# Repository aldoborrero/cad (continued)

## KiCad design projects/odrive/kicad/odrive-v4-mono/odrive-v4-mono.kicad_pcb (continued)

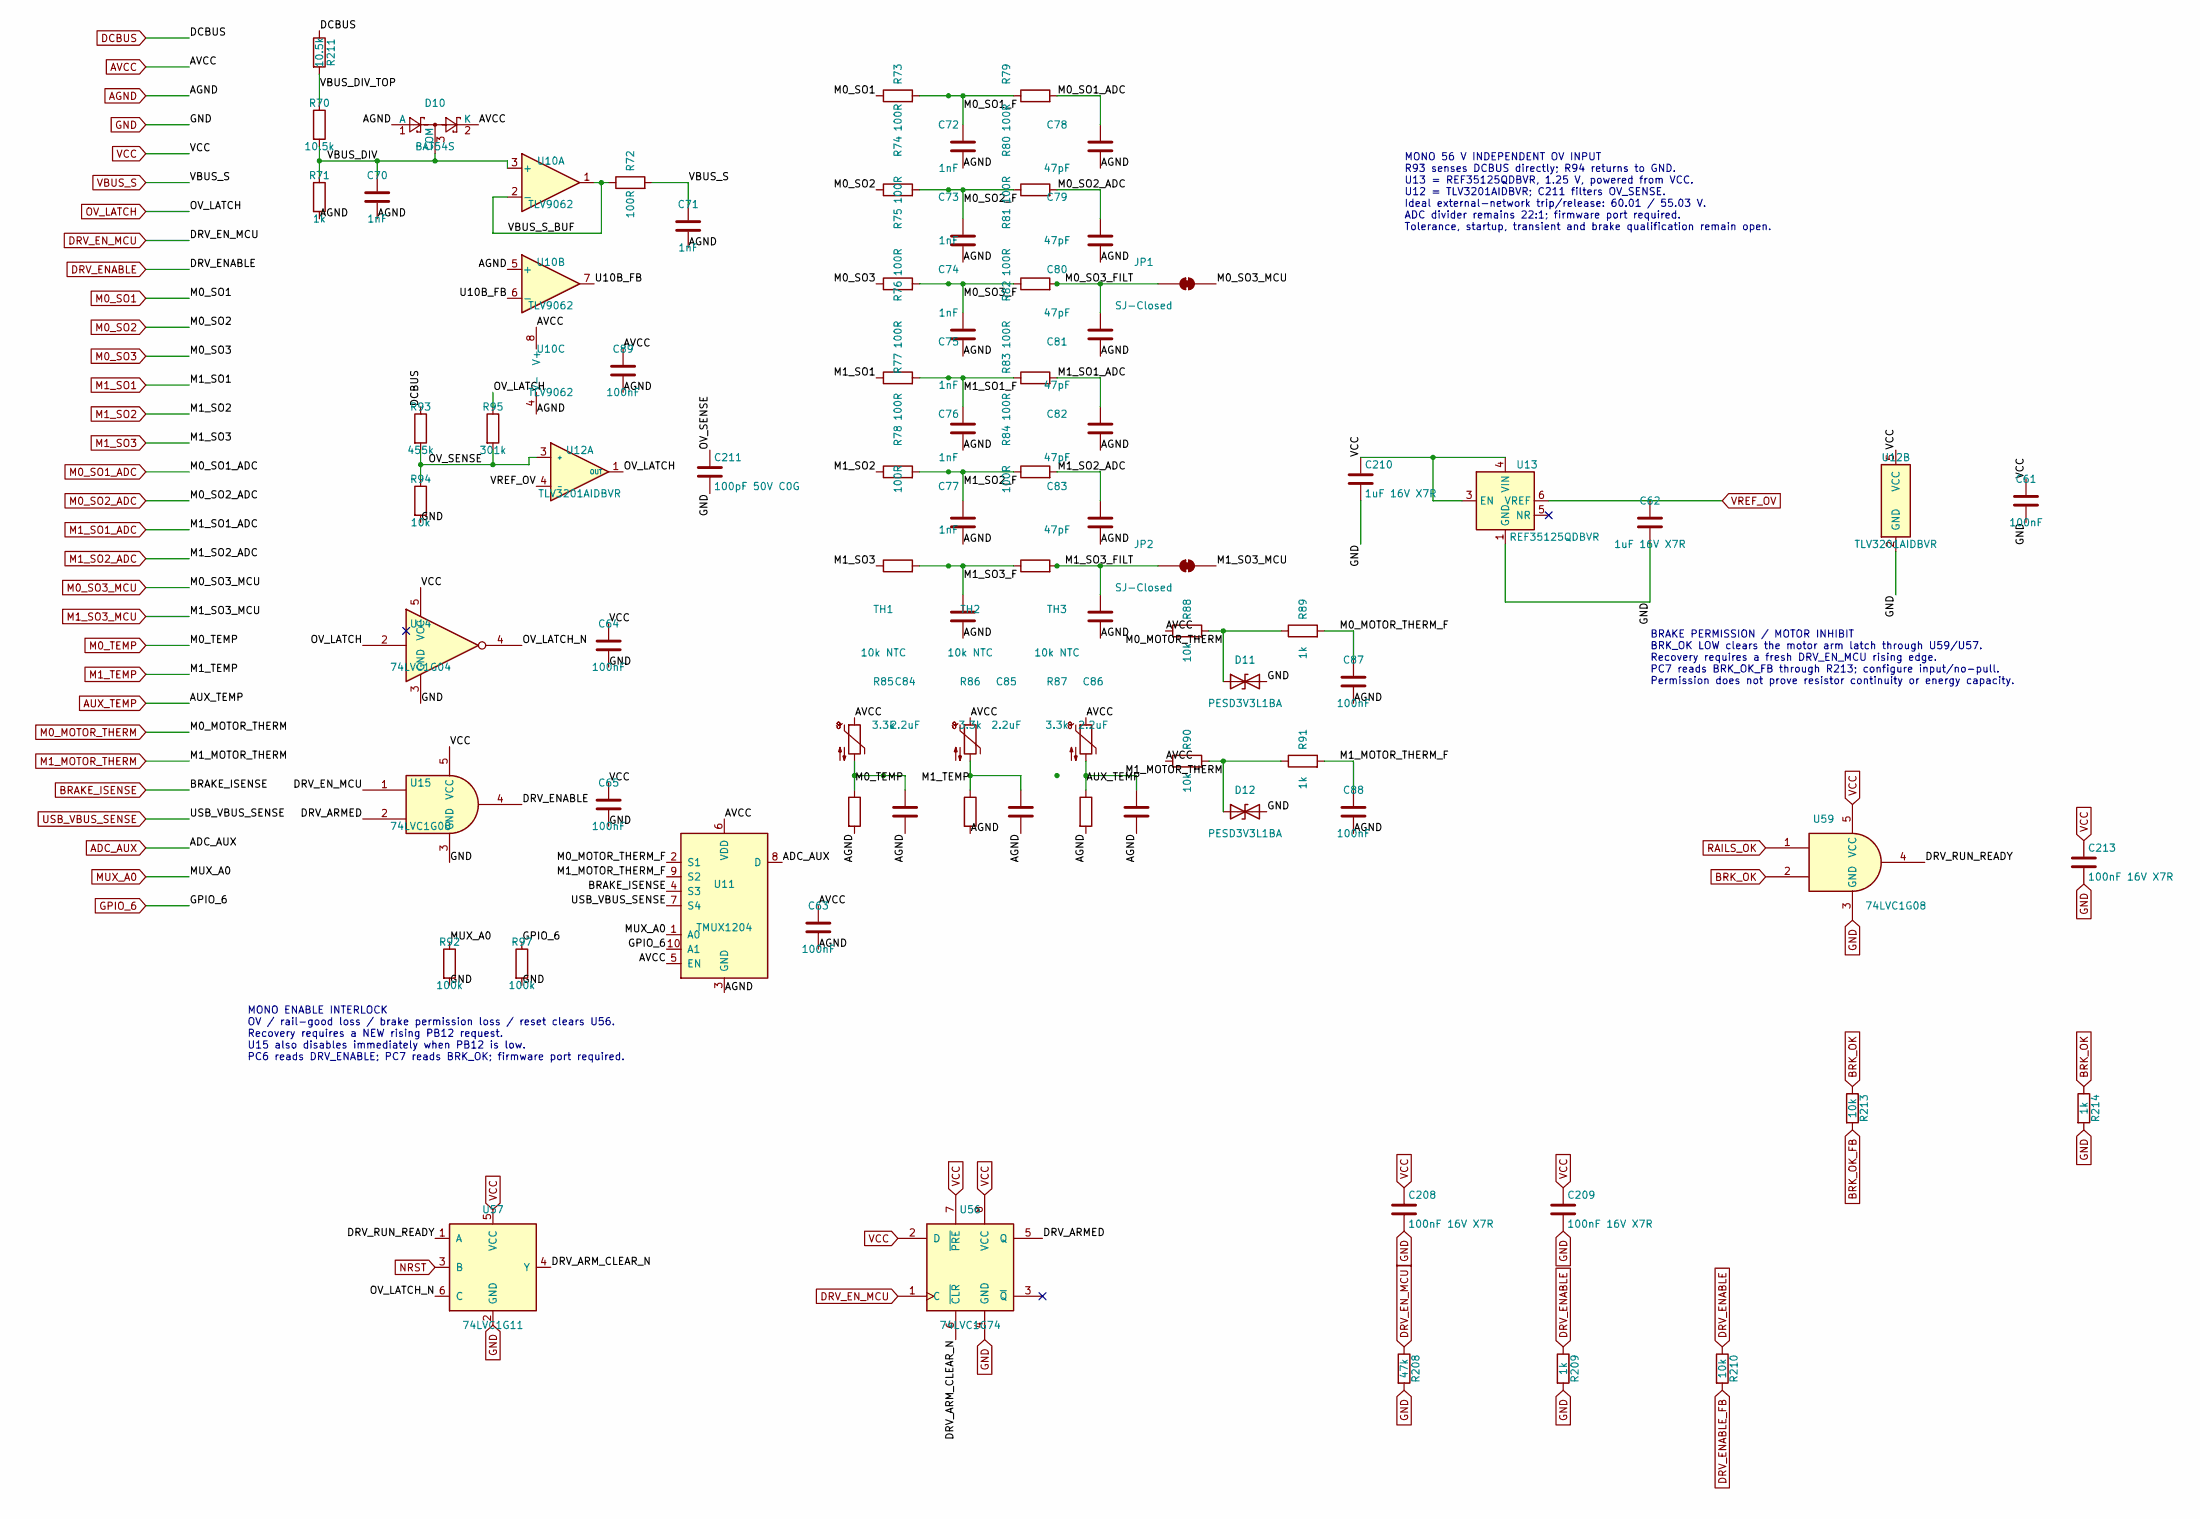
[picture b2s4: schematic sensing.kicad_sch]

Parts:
C61, C63, C64, C65, C87, C88, C89: 100nF; C_0603_1608Metric
C62, C210: 1uF 16V X7R; C_0603_1608Metric; Tolerance 10%
C70, C71, C72, C73, C74, C75, C76, C77: 1nF; C_0603_1608Metric
C78, C79, C80, C81, C82, C83: 47pF; C_0603_1608Metric
C84, C85, C86: 2.2uF; C_0603_1608Metric
C208, C209: 100nF 16V X7R; C_0603_1608Metric
C211: 100pF 50V C0G; C_0603_1608Metric; Tolerance 5%
C213: 100nF 16V X7R; C_0603_1608Metric; Tolerance 10%
D10: BAT54S; SOT-23
D11, D12: PESD3V3L1BA; D_SOD-323
JP1, JP2: SJ-Closed; SolderJumper-2_P1.3mm_Bridged_Pad1.0x1.5mm
R70, R211: 10.5k; R_1206_3216Metric; Tolerance 0.1%; Voltage 200 V minimum working
R71: 1k; R_0603_1608Metric; Tolerance 0.1%
R72, R73, R74, R75, R76, R77, R78, R79, R80, R81, R82, R83, R84: 100R; R_0603_1608Metric
R85, R86, R87: 3.3k; R_0603_1608Metric
R88, R90: 10k; R_0603_1608Metric
R89, R91: 1k; R_0603_1608Metric
R92, R97: 100k; R_0603_1608Metric
R93: 455k; R_1206_3216Metric; Tolerance 0.1%; Working voltage 200 V minimum
R94: 10k; R_0603_1608Metric; Tolerance 0.1%
R95: 301k; R_0603_1608Metric; Tolerance 0.1%
R208: 47k; R_0603_1608Metric; Tolerance 1%
R209, R214: 1k; R_0603_1608Metric; Tolerance 1%
R210, R213: 10k; R_0603_1608Metric; Tolerance 1%
TH1, TH2, TH3: 10k NTC; R_0603_1608Metric
U10: TLV9062; SOIC-8_3.9x4.9mm_P1.27mm
U11: TMUX1204; MSOP-10_3x3mm_P0.5mm; MPN TMUX1204DGSR
U12: TLV3201AIDBVR; SOT-23-5; MPN TLV3201AIDBVR
U13: REF35125QDBVR; SOT-23-6; MPN REF35125QDBVR
U14: 74LVC1G04; SOT-23-5; MPN SN74LVC1G04DBVR
U15, U59: 74LVC1G08; SOT-23-5; MPN SN74LVC1G08DBVR
U56: 74LVC1G74; VSSOP-8_2.3x2mm_P0.5mm; MPN SN74LVC1G74DCUR
U57: 74LVC1G11; SOT-23-6; MPN SN74LVC1G11DBVR

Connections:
/Sensing/DRV_ARMED: U15.2, U56.5 (Q)
/Sensing/DRV_ARM_CLEAR_N: U56.6 (~CLR), U57.4 (Y)
/Sensing/DRV_RUN_READY: U57.1 (A), U59.4
/Sensing/M0_MOTOR_THERM_F: C87.1, R89.2, U11.2 (S1)
/Sensing/M0_SO1_F: C72.1, R73.2, R79.1
/Sensing/M0_SO2_F: C73.1, R74.2, R80.1
/Sensing/M0_SO3_F: C76.1, R77.2, R83.1
/Sensing/M0_SO3_FILT: C82.1, JP1.1 (A), R83.2
/Sensing/M1_MOTOR_THERM_F: C88.1, R91.2, U11.9 (S2)
/Sensing/M1_SO1_F: C75.1, R76.2, R82.1
/Sensing/M1_SO2_F: C74.1, R75.2, R81.1
/Sensing/M1_SO3_F: C77.1, R78.2, R84.1
/Sensing/M1_SO3_FILT: C83.1, JP2.1 (A), R84.2
/Sensing/OV_LATCH_N: U14.4, U57.6 (C)
/Sensing/OV_SENSE: C211.1, R93.2, R94.1, R95.2, U12.3 (+)
/Sensing/U10B_FB: U10.6 (-), U10.7
/Sensing/VBUS_DIV: C70.1, D10.3 (COM), R70.2, R71.1, U10.3 (+)
/Sensing/VBUS_DIV_TOP: R70.1, R211.2
/Sensing/VBUS_S_BUF: R72.1, U10.1, U10.2 (-)
ADC_AUX: U11.8 (D); also elsewhere on the board
AGND: C63.2, C70.2, C71.2, C72.2, C73.2, C74.2, C75.2, C76.2, C77.2, C78.2, C79.2, C80.2, C81.2, C82.2, C83.2, C84.2, C85.2, C86.2, C87.2, C88.2, C89.2, D10.1 (A), R71.2, R85.2, R86.2, R87.2, U10.4 (V-), U10.5 (+), U11.3 (GND); also elsewhere on the board
AUX_TEMP: C86.1, R87.1, TH3.2; also elsewhere on the board
AVCC: C63.1, C89.1, D10.2 (K), R88.1, R90.1, TH1.1, TH2.1, TH3.1, U10.8 (V+), U11.5 (EN), U11.6 (VDD); also elsewhere on the board
BRAKE_ISENSE: U11.4 (S3); also elsewhere on the board
BRK_OK: R213.1, R214.1, U59.2; also elsewhere on the board
BRK_OK_FB: R213.2; also elsewhere on the board
DCBUS: R93.1, R211.1; also elsewhere on the board
DRV_ENABLE: R209.1, R210.1, U15.4; also elsewhere on the board
DRV_ENABLE_FB: R210.2; also elsewhere on the board
DRV_EN_MCU: R208.1, U15.1, U56.1 (C); also elsewhere on the board
GND: C61.2, C62.2, C64.2, C65.2, C208.2, C209.2, C210.2, C211.2, C213.2, D11.2 (A2), D12.2 (A2), R92.2, R94.2, R97.2, R208.2, R209.2, R214.2, U12.2 (GND), U13.1 (GND), U13.2 (GND), U14.3 (GND), U15.3 (GND), U56.4 (GND), U57.2 (GND), U59.3 (GND); also elsewhere on the board
GPIO_6: R97.1, U11.10 (A1); also elsewhere on the board
M0_MOTOR_THERM: D11.1 (A1), R88.2, R89.1; also elsewhere on the board
M0_SO1: R73.1; also elsewhere on the board
M0_SO1_ADC: C78.1, R79.2; also elsewhere on the board
M0_SO2: R74.1; also elsewhere on the board
M0_SO2_ADC: C79.1, R80.2; also elsewhere on the board
M0_SO3: R77.1; also elsewhere on the board
M0_SO3_MCU: JP1.2 (B); also elsewhere on the board
M0_TEMP: C84.1, R85.1, TH1.2; also elsewhere on the board
M1_MOTOR_THERM: D12.1 (A1), R90.2, R91.1; also elsewhere on the board
M1_SO1: R76.1
M1_SO1_ADC: C81.1, R82.2; also elsewhere on the board
M1_SO2: R75.1
M1_SO2_ADC: C80.1, R81.2; also elsewhere on the board
M1_SO3: R78.1
M1_SO3_MCU: JP2.2 (B); also elsewhere on the board
M1_TEMP: C85.1, R86.1, TH2.2; also elsewhere on the board
MUX_A0: R92.1, U11.1 (A0); also elsewhere on the board
NRST: U57.3 (B); also elsewhere on the board
OV_LATCH: R95.1, U12.1 (OUT), U14.2; also elsewhere on the board
RAILS_OK: U59.1; also elsewhere on the board
USB_VBUS_SENSE: U11.7 (S4); also elsewhere on the board
VBUS_S: C71.1, R72.2; also elsewhere on the board
VCC: C61.1, C64.1, C65.1, C208.1, C209.1, C210.1, C213.1, U12.5 (VCC), U13.3 (EN), U13.4 (VIN), U14.5 (VCC), U15.5 (VCC), U56.2 (D), U56.7 (~PRE), U56.8 (VCC), U57.5 (VCC), U59.5 (VCC); also elsewhere on the board
VREF_OV: C62.1, U12.4 (-), U13.6 (VREF); also elsewhere on the board

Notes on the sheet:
MONO 56 V INDEPENDENT OV INPUT R93 senses DCBUS directly; R94 returns to GND. U13 = REF35125QDBVR, 1.25 V, powered from VCC. U12 = TLV3201AIDBVR; C211 filters OV_SENSE. Ideal external-network trip/release: 60.01 / 55.03 V. ADC divider remains 22:1; firmware port required. Tolerance, startup, transi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
BRAKE PERMISSION / MOTOR INHIBIT BRK_OK LOW clears the motor arm latch through U59/U57. Recovery requires a fresh DRV_EN_MCU rising edge. PC7 reads BRK_OK_FB through R213; configure input/no-pull. Permission does not prove resistor continuity or energy capacity.
MONO ENABLE INTERLOCK OV / rail-good loss / brake permission loss / reset clears U56. Recovery requires a NEW rising PB12 request. U15 also disables immediately when PB12 is low. PC6 reads DRV_ENABLE; PC7 reads BRK_OK; firmware port required.

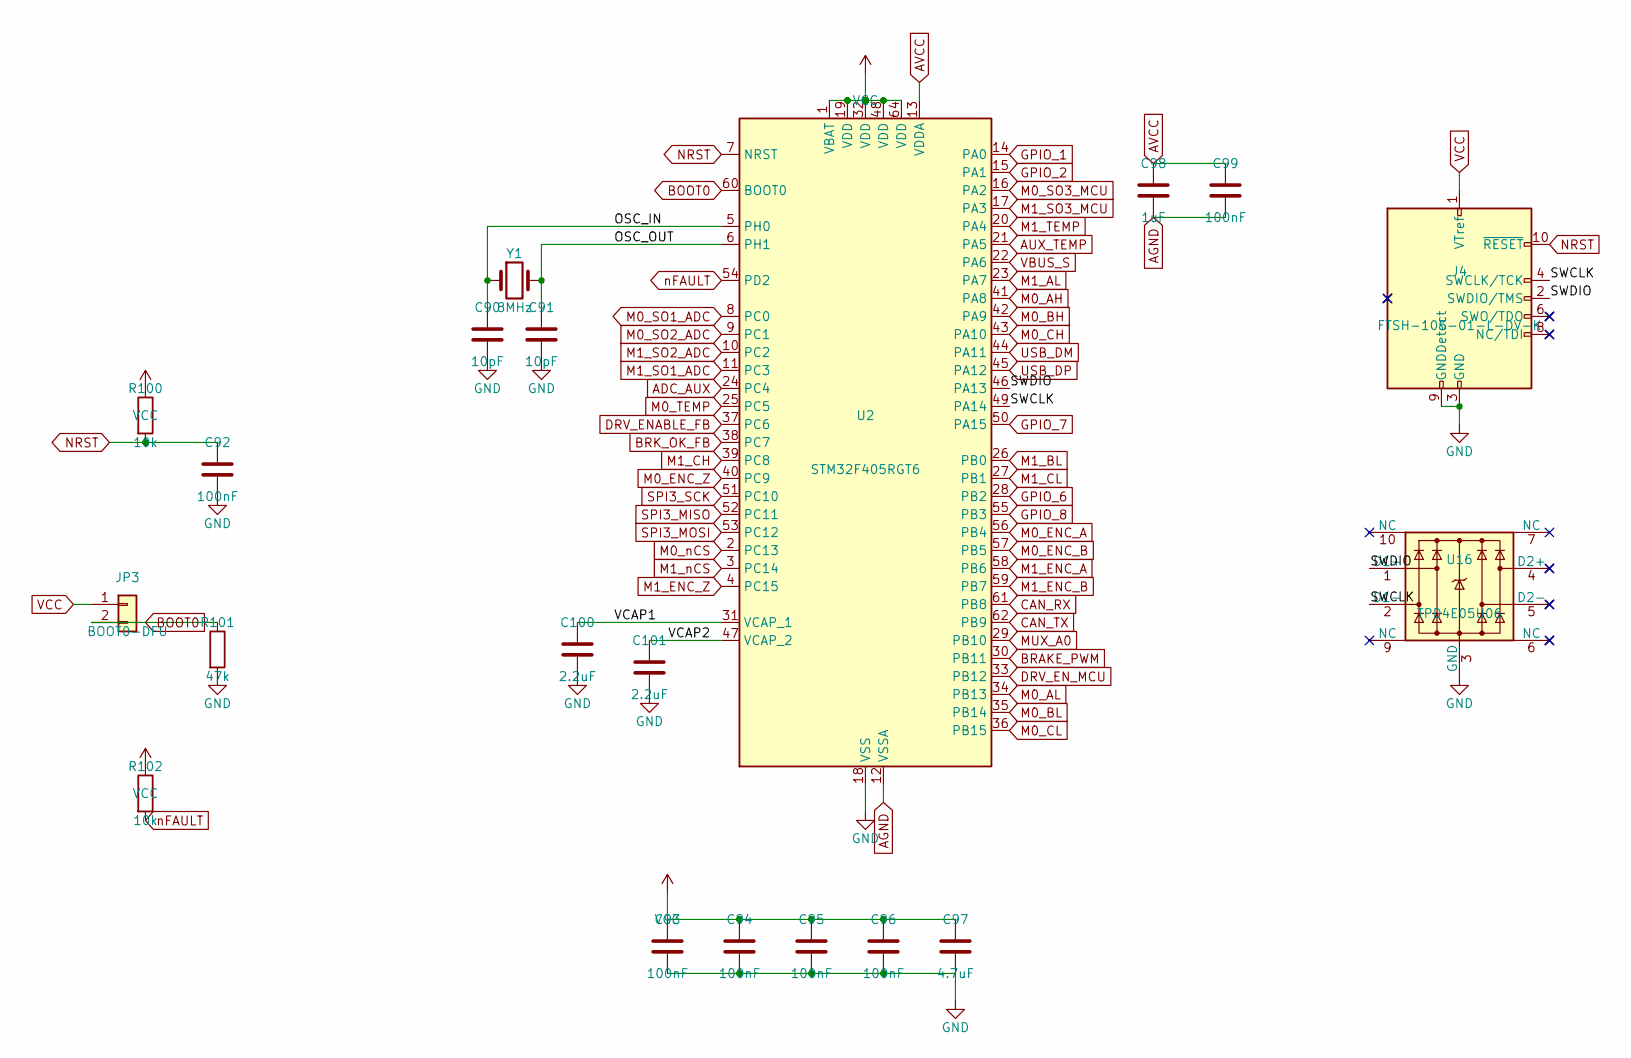
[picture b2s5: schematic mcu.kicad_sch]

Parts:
C90, C91: 10pF; C_0603_1608Metric
C92, C93, C94, C95, C96, C99: 100nF; C_0603_1608Metric
C97: 4.7uF; C_0805_2012Metric
C98: 1uF; C_0603_1608Metric
C100, C101: 2.2uF; C_0603_1608Metric
J4: FTSH-105-01-L-DV-K; PinHeader_2x05_P1.27mm_Vertical_SMD
JP3: BOOT0-DFU; PinHeader_1x02_P2.54mm_Vertical
R100, R102: 10k; R_0603_1608Metric
R101: 47k; R_0603_1608Metric
U2: STM32F405RGT6; LQFP-64_10x10mm_P0.5mm
U16: TPD4E05U06; USON-10_2.5x1.0mm_P0.5mm
Y1: 8MHz; Crystal_SMD_5032-2Pin_5.0x3.2mm

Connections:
/MCU/OSC_IN: C90.1, U2.5 (PH0), Y1.1
/MCU/OSC_OUT: C91.1, U2.6 (PH1), Y1.2
/MCU/SWCLK: J4.4 (SWCLK/TCK), U2.49 (PA14), U16.2 (D1-)
/MCU/SWDIO: J4.2 (SWDIO/TMS), U2.46 (PA13), U16.1 (D1+)
/MCU/VCAP1: C100.1, U2.31 (VCAP_1)
/MCU/VCAP2: C101.1, U2.47 (VCAP_2)
ADC_AUX: U2.24 (PC4); also elsewhere on the board
AGND: C98.2, C99.2, U2.12 (VSSA); also elsewhere on the board
AUX_TEMP: U2.21 (PA5); also elsewhere on the board
AVCC: C98.1, C99.1, U2.13 (VDDA); also elsewhere on the board
BOOT0: JP3.2, R101.1, U2.60 (BOOT0)
BRAKE_PWM: U2.30 (PB11); also elsewhere on the board
BRK_OK_FB: U2.38 (PC7); also elsewhere on the board
CAN_RX: U2.61 (PB8); also elsewhere on the board
CAN_TX: U2.62 (PB9); also elsewhere on the board
DRV_ENABLE_FB: U2.37 (PC6); also elsewhere on the board
DRV_EN_MCU: U2.33 (PB12); also elsewhere on the board
GND: C90.2, C91.2, C92.2, C93.2, C94.2, C95.2, C96.2, C97.2, C100.2, C101.2, J4.3 (GND), J4.5 (GND), J4.9 (GNDDetect), R101.2, U2.18 (VSS), U2.63 (VSS), U16.3 (GND), U16.8 (GND); also elsewhere on the board
GPIO_1: U2.14 (PA0); also elsewhere on the board
GPIO_2: U2.15 (PA1); also elsewhere on the board
GPIO_6: U2.28 (PB2); also elsewhere on the board
GPIO_7: U2.50 (PA15); also elsewhere on the board
GPIO_8: U2.55 (PB3); also elsewhere on the board
M0_AH: U2.41 (PA8); also elsewhere on the board
M0_AL: U2.34 (PB13); also elsewhere on the board
M0_BH: U2.42 (PA9); also elsewhere on the board
M0_BL: U2.35 (PB14); also elsewhere on the board
M0_CH: U2.43 (PA10); also elsewhere on the board
M0_CL: U2.36 (PB15); also elsewhere on the board
M0_ENC_A: U2.56 (PB4); also elsewhere on the board
M0_ENC_B: U2.57 (PB5); also elsewhere on the board
M0_ENC_Z: U2.40 (PC9); also elsewhere on the board
M0_SO1_ADC: U2.8 (PC0); also elsewhere on the board
M0_SO2_ADC: U2.9 (PC1); also elsewhere on the board
M0_SO3_MCU: U2.16 (PA2); also elsewhere on the board
M0_TEMP: U2.25 (PC5); also elsewhere on the board
M0_nCS: U2.2 (PC13); also elsewhere on the board
M1_AL: U2.23 (PA7)
M1_BL: U2.26 (PB0)
M1_CH: U2.39 (PC8)
M1_CL: U2.27 (PB1)
M1_ENC_A: U2.58 (PB6); also elsewhere on the board
M1_ENC_B: U2.59 (PB7); also elsewhere on the board
M1_ENC_Z: U2.4 (PC15); also elsewhere on the board
M1_SO1_ADC: U2.11 (PC3); also elsewhere on the board
M1_SO2_ADC: U2.10 (PC2); also elsewhere on the board
M1_SO3_MCU: U2.17 (PA3); also elsewhere on the board
M1_TEMP: U2.20 (PA4); also elsewhere on the board
M1_nCS: U2.3 (PC14)
MUX_A0: U2.29 (PB10); also elsewhere on the board
NRST: C92.1, J4.10 (~RESET), R100.2, U2.7 (NRST); also elsewhere on the board
SPI3_MISO: U2.52 (PC11); also elsewhere on the board
SPI3_MOSI: U2.53 (PC12); also elsewhere on the board
SPI3_SCK: U2.51 (PC10); also elsewhere on the board
USB_DM: U2.44 (PA11); also elsewhere on the board
USB_DP: U2.45 (PA12); also elsewhere on the board
VBUS_S: U2.22 (PA6); also elsewhere on the board
VCC: C93.1, C94.1, C95.1, C96.1, C97.1, J4.1 (VTref), JP3.1, R100.1, R102.1, U2.1 (VBAT), U2.19 (VDD), U2.32 (VDD), U2.48 (VDD), U2.64 (VDD); also elsewhere on the board
nFAULT: R102.2, U2.54 (PD2); also elsewhere on the board

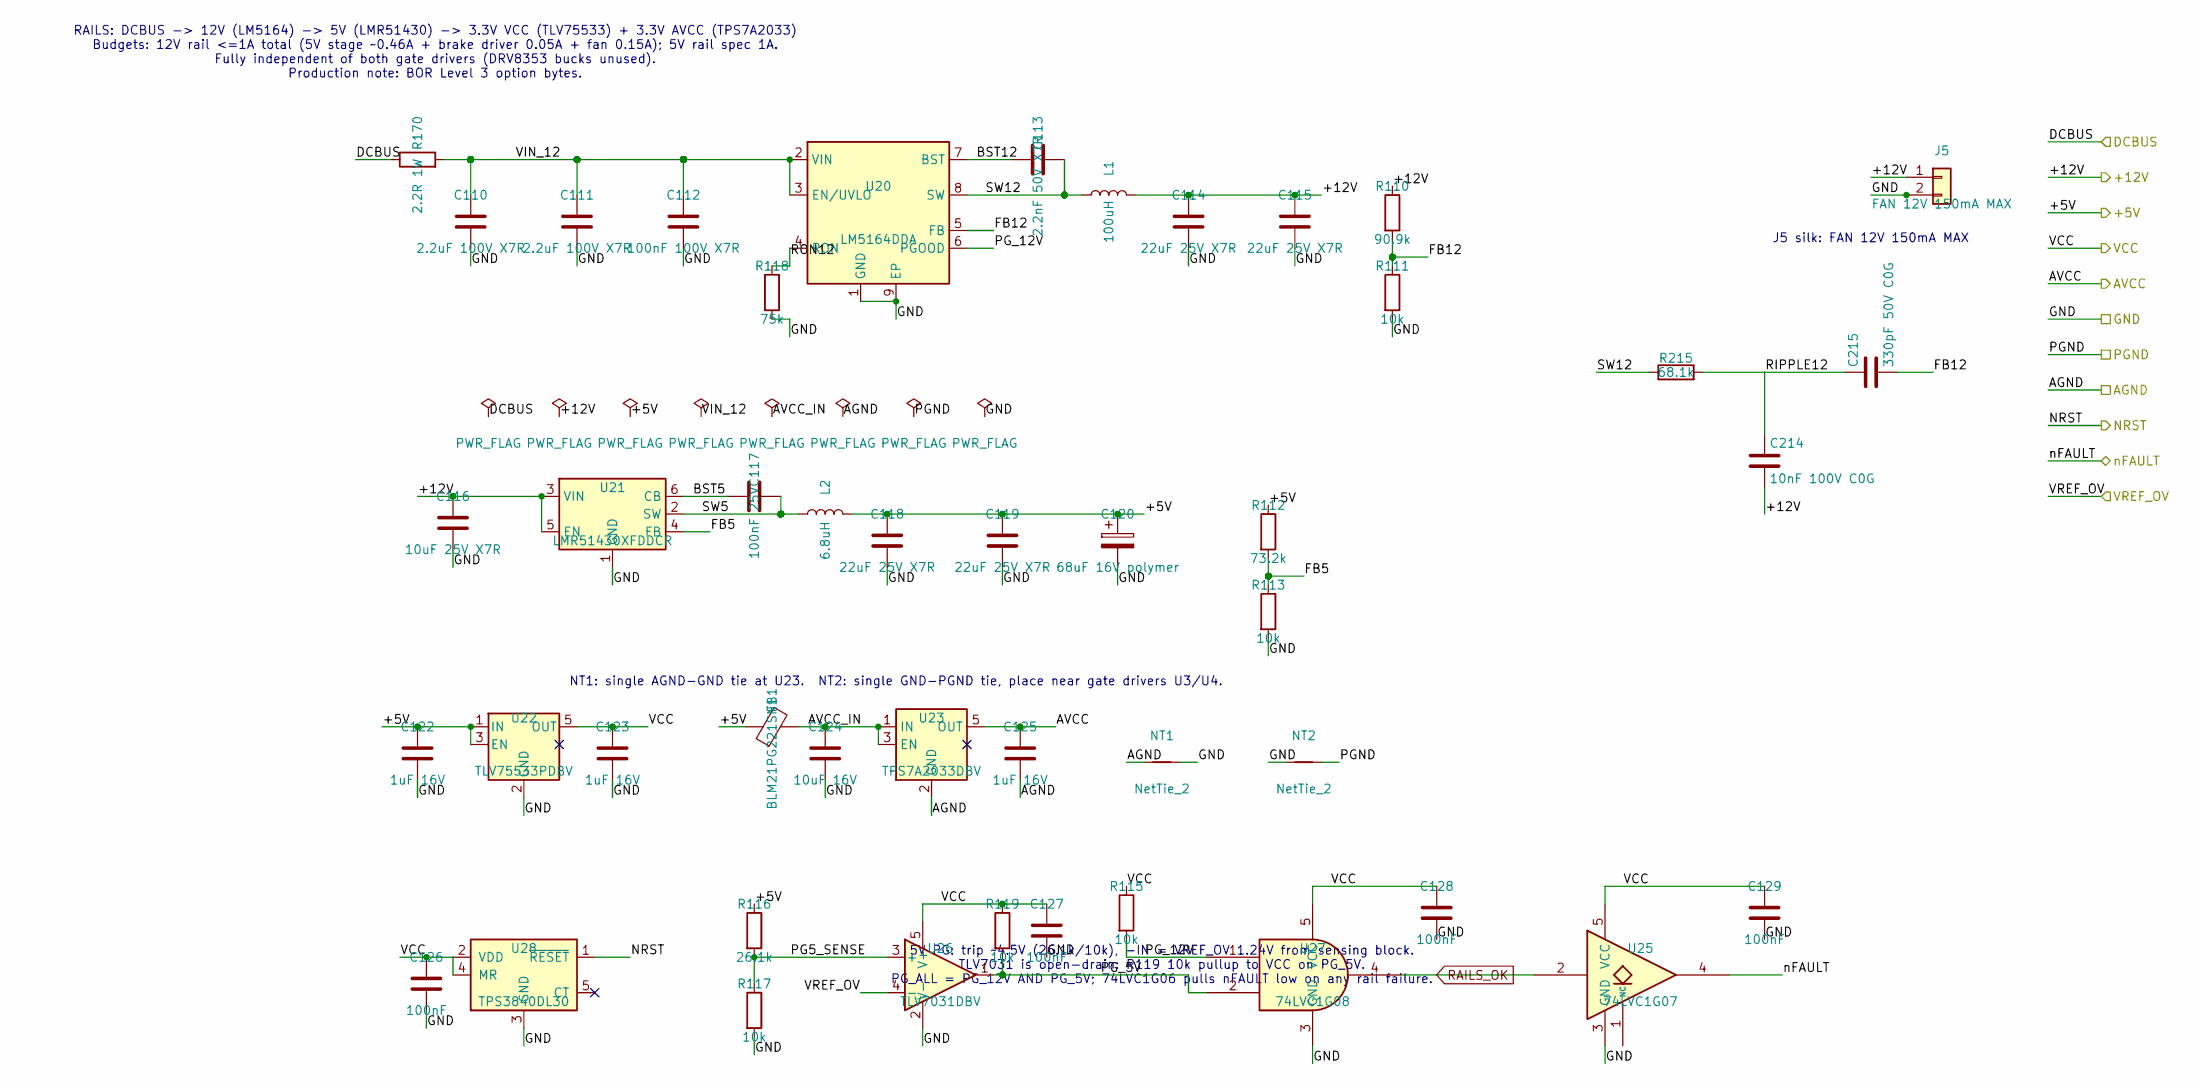
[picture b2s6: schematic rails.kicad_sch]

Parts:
C110, C111: 2.2uF 100V X7R; C_1210_3225Metric
C112: 100nF 100V X7R; C_0603_1608Metric
C113: 2.2nF 50V X7R; C_0603_1608Metric; Tolerance 5%
C114, C115, C118, C119: 22uF 25V X7R; C_1210_3225Metric
C116: 10uF 25V X7R; C_0805_2012Metric
C117: 100nF 25V; C_0603_1608Metric
C120: 68uF 16V polymer; CP_Elec_6.3x7.7
C122, C123, C125: 1uF 16V; C_0603_1608Metric
C124: 10uF 16V; C_0805_2012Metric
C126, C127, C128, C129: 100nF; C_0603_1608Metric
C214: 10nF 100V C0G; C_0603_1608Metric; Tolerance 5%
C215: 330pF 50V C0G; C_0603_1608Metric; Tolerance 5%
FB1: BLM21PG221SN1; L_0805_2012Metric
J5: FAN 12V 150mA MAX; PinHeader_1x02_P2.54mm_Vertical
L1: 100uH; L_Wuerth_WE-PD-Typ-LS; Tolerance 20%; MPN 7447709101; LCSC C6463690
L2: 6.8uH; Coilcraft_XAL7070_682; Tolerance 20%; MPN XAL7070-682MEC; LCSC C3911753
NT1, NT2: NetTie_2; NetTie-2_SMD_Pad0.5mm
R110: 90.9k; R_0603_1608Metric; Tolerance 1%
R111: 10k; R_0603_1608Metric; Tolerance 1%
R112: 73.2k; R_0603_1608Metric
R113, R115, R117, R119: 10k; R_0603_1608Metric
R116: 26.1k; R_0603_1608Metric
R118: 75k; R_0603_1608Metric; Tolerance 1%
R170: 2.2R 1W; R_2512_6332Metric
R215: 68.1k; R_0805_2012Metric; Tolerance 1%
U20: LM5164DDA; HSOP-8-1EP_3.9x4.9mm_P1.27mm_EP2.41x3.1mm_ThermalVias; MPN LM5164DDAR
U21: LMR51430XFDDCR; TI_DDC0006A; MPN LMR51430XFDDCR; LCSC C5219260
U22: TLV75533PDBV; SOT-23-5
U23: TPS7A2033DBV; SOT-23-5
U25: 74LVC1G07; SOT-23-5; MPN SN74LVC1G07DBVR
U26: TLV7031DBV; SOT-23-5
U27: 74LVC1G08; SOT-23-5; MPN SN74LVC1G08DBVR
U28: TPS3840DL30; SOT-23-5; MPN TPS3840DL30DBVR

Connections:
+5V: C118.1, C119.1, C120.1, C122.1, FB1.1, L2.2, R112.1, R116.1, U22.1 (IN), U22.3 (EN); also elsewhere on the board
+12V: C114.1, C115.1, C116.1, C214.2, J5.1, L1.2, R110.1, U21.3 (VIN), U21.5 (EN); also elsewhere on the board
/Rails/AVCC_IN: C124.1, FB1.2, U23.1 (IN), U23.3 (EN)
/Rails/BST5: C117.1, U21.6 (CB)
/Rails/BST12: C113.1, U20.7 (BST)
/Rails/FB5: R112.2, R113.1, U21.4 (FB)
/Rails/FB12: C215.2, R110.2, R111.1, U20.5 (FB)
/Rails/PG5_SENSE: R116.2, R117.1, U26.3 (+)
/Rails/PG_5V: R119.2, U26.1, U27.2
/Rails/PG_12V: R115.2, U20.6 (PGOOD), U27.1
/Rails/RIPPLE12: C214.1, C215.1, R215.2
/Rails/RON12: R118.1, U20.4 (RON)
/Rails/SW5: C117.2, L2.1, U21.2 (SW)
/Rails/SW12: C113.2, L1.1, R215.1, U20.8 (SW)
/Rails/VIN_12: C110.1, C111.1, C112.1, R170.2, U20.2 (VIN), U20.3 (EN/UVLO)
AGND: C125.2, NT1.1, U23.2 (GND); also elsewhere on the board
AVCC: C125.1, U23.5 (OUT); also elsewhere on the board
DCBUS: R170.1; also elsewhere on the board
GND: C110.2, C111.2, C112.2, C114.2, C115.2, C116.2, C118.2, C119.2, C120.2, C122.2, C123.2, C124.2, C126.2, C127.2, C128.2, C129.2, J5.2, NT1.2, NT2.1, R111.2, R113.2, R117.2, R118.2, U20.1 (GND), U20.9 (EP), U21.1 (GND), U22.2 (GND), U25.3 (GND), U26.2 (V-), U27.3 (GND), U28.3 (GND); also elsewhere on the board
NRST: U28.1 (~RESET); also elsewhere on the board
PGND: NT2.2; also elsewhere on the board
RAILS_OK: U25.2, U27.4; also elsewhere on the board
VCC: C123.1, C126.1, C127.1, C128.1, C129.1, R115.1, R119.1, U22.5 (OUT), U25.5 (VCC), U26.5 (V+), U27.5 (VCC), U28.2 (VDD), U28.4 (MR); also elsewhere on the board
VREF_OV: U26.4 (-); also elsewhere on the board
nFAULT: U25.4; also elsewhere on the board

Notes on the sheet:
RAILS: DCBUS -> 12V (LM5164) -> 5V (LMR51430) -> 3.3V VCC (TLV75533) + 3.3V AVCC (TPS7A2033) Budgets: 12V rail <=1A total (5V stage ~0.46A + brake driver 0.05A + fan 0.15A); 5V rail spec 1A. Fully independent of both gate drivers (DRV8353 bucks unused). Production note: BOR Level 3 option bytes.
NT1: single AGND-GND tie at U23. NT2: single GND-PGND tie, place near gate drivers U3/U4.
J5 silk: FAN 12V 150mA MAX
5V PG: trip ~4.5V (26.1k/10k), -IN = VREF_OV 1.24V from sensing block. TLV7031 is open-drain: R119 10k pullup to VCC on PG_5V. PG_ALL = PG_12V AND PG_5V; 74LVC1G06 pulls nFAULT low on any rail failure.

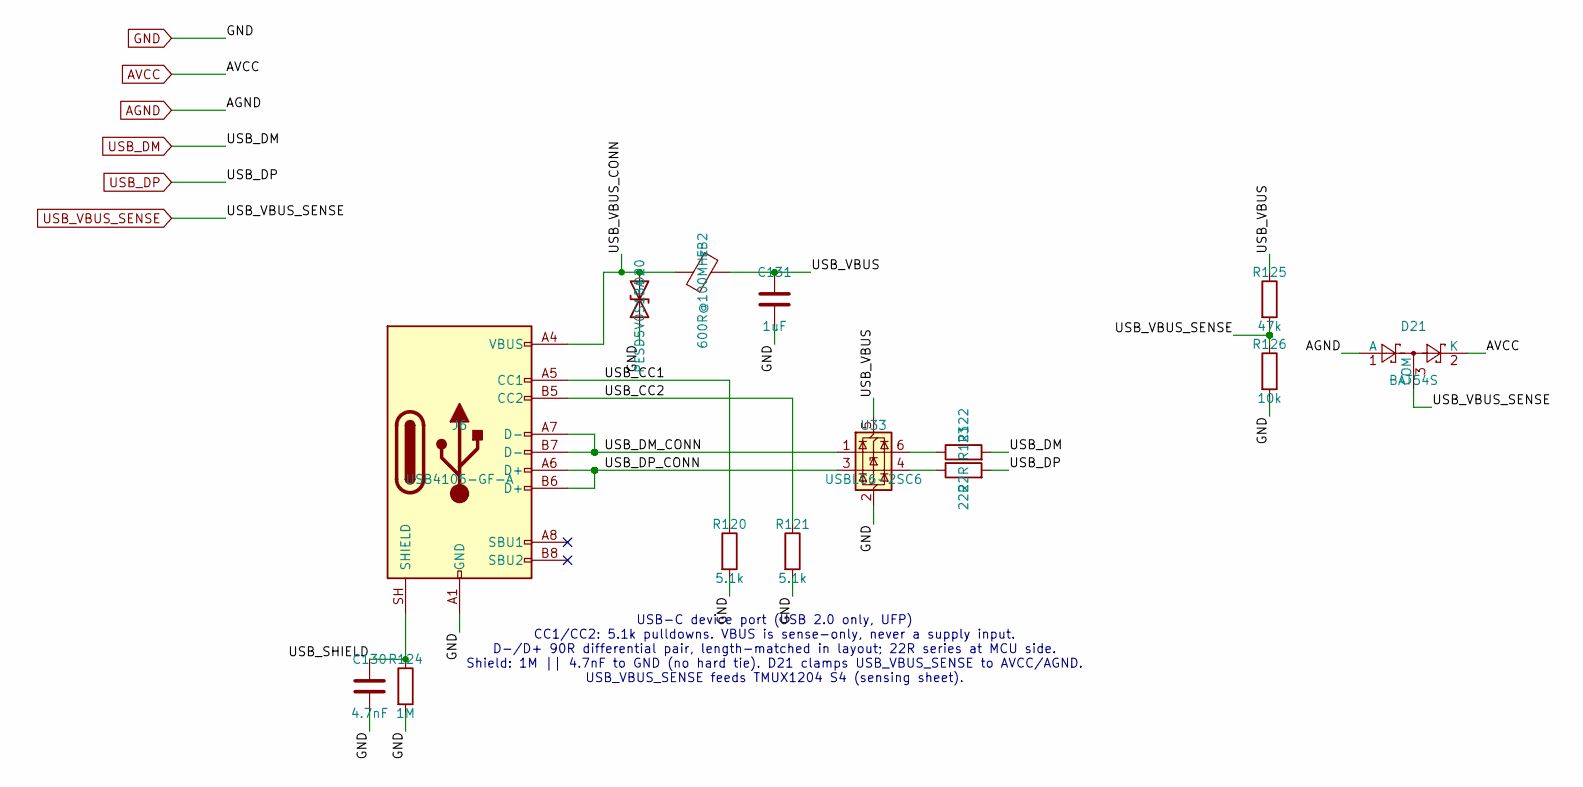
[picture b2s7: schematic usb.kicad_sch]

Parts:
C130: 4.7nF; C_0603_1608Metric
C131: 1uF; C_0603_1608Metric
D20: PESD5V0S1BA; D_SOD-323
D21: BAT54S; SOT-23
FB2: 600R@100MHz; L_0805_2012Metric
J6: USB4105-GF-A; USB_C_Receptacle_GCT_USB4105-xx-A_16P_TopMnt_Horizontal
R120, R121: 5.1k; R_0603_1608Metric
R122, R123: 22R; R_0603_1608Metric
R124: 1M; R_0603_1608Metric
R125: 47k; R_0603_1608Metric
R126: 10k; R_0603_1608Metric
U33: USBLC6-2SC6; SOT-23-6

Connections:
/USB/USB_CC1: J6.A5 (CC1), R120.1
/USB/USB_CC2: J6.B5 (CC2), R121.1
/USB/USB_DM_CONN: J6.A7 (D-), J6.B7 (D-), U33.1 (I/O1)
/USB/USB_DP_CONN: J6.A6 (D+), J6.B6 (D+), U33.3 (I/O2)
/USB/USB_SHIELD: C130.1, J6.SH (SHIELD), R124.1
/USB/USB_VBUS: C131.1, FB2.2, R125.1, U33.5 (VBUS)
/USB/USB_VBUS_CONN: D20.2 (A2), FB2.1, J6.A4 (VBUS), J6.A9 (VBUS), J6.B4 (VBUS), J6.B9 (VBUS)
AGND: D21.1 (A); also elsewhere on the board
AVCC: D21.2 (K); also elsewhere on the board
GND: C130.2, C131.2, D20.1 (A1), J6.A1 (GND), J6.A12 (GND), J6.B1 (GND), J6.B12 (GND), R120.2, R121.2, R124.2, R126.2, U33.2 (GND); also elsewhere on the board
unnamed: R122.1, U33.6 (I/O1)
unnamed: R123.1, U33.4 (I/O2)
USB_DM: R122.2; also elsewhere on the board
USB_DP: R123.2; also elsewhere on the board
USB_VBUS_SENSE: D21.3 (COM), R125.2, R126.1; also elsewhere on the board

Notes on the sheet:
USB-C device port (USB 2.0 only, UFP) CC1/CC2: 5.1k pulldowns. VBUS is sense-only, never a supply input. D-/D+ 90R differential pair, length-matched in layout; 22R series at MCU side. Shield: 1M || 4.7nF to GND (no hard tie). D21 clamps USB_VBUS_SENSE to AVCC/AGND. USB_VBUS_SENSE feeds TMUX1204 S4 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

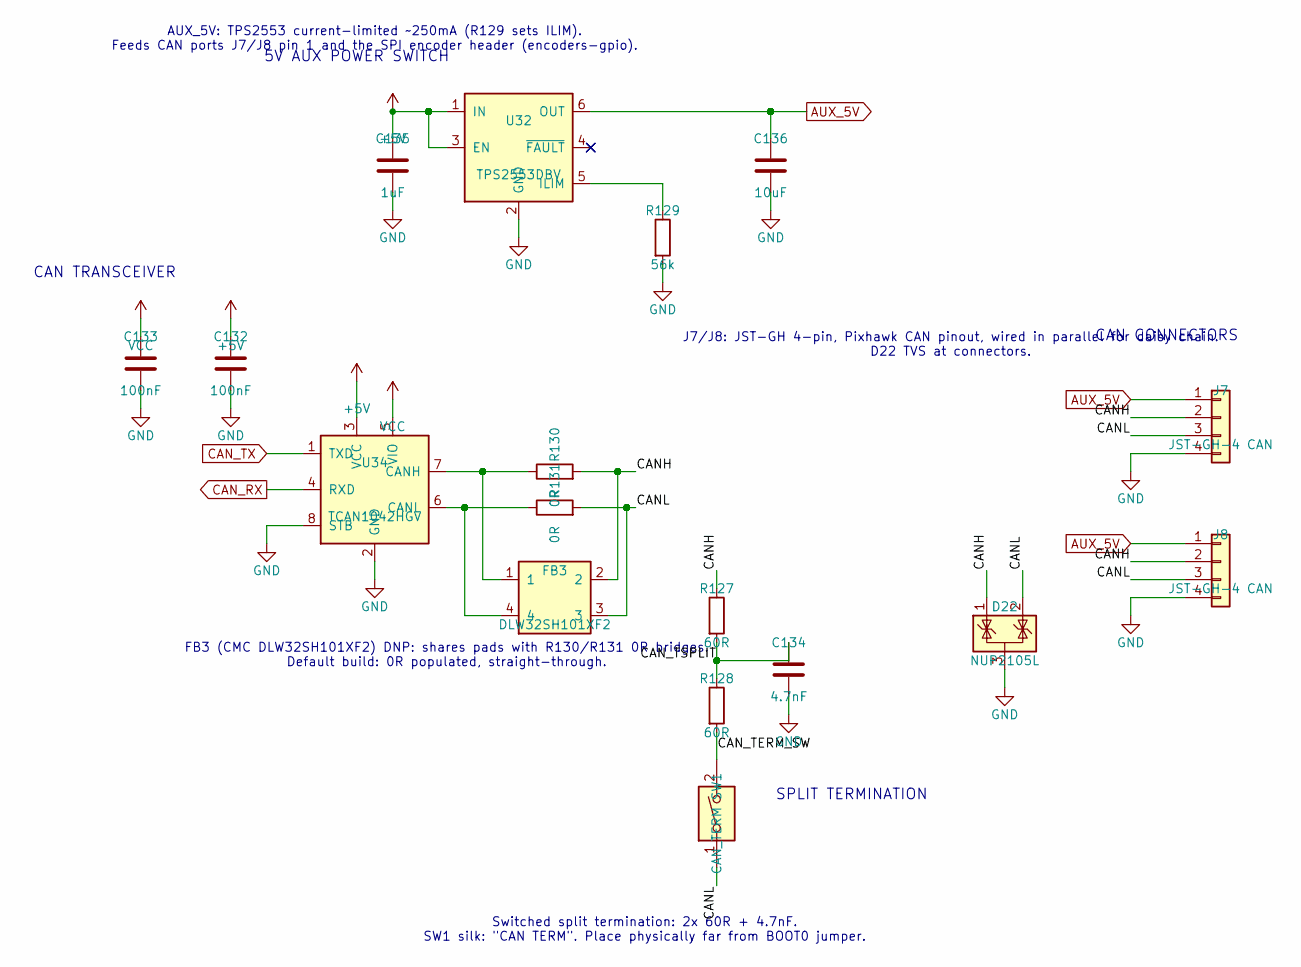
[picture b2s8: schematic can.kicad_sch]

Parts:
C132, C133: 100nF; C_0603_1608Metric
C134: 4.7nF; C_0603_1608Metric
C135: 1uF; C_0603_1608Metric
C136: 10uF; C_0805_2012Metric
D22: NUP2105L; SOT-23
FB3: DLW32SH101XF2; L_CommonMode_Murata_DLW32SH101XF2
J7, J8: JST-GH-4 CAN; JST_GH_BM04B-GHS-TBT_1x04-1MP_P1.25mm_Vertical
R127, R128: 60R; R_0603_1608Metric
R129: 56k; R_0603_1608Metric
R130, R131: 0R; R_0603_1608Metric
SW1: CAN_TERM; SW_DIP_SPSTx01_Slide_9.78x4.72mm_W7.62mm_P2.54mm
U32: TPS2553DBV; SOT-23-6; MPN TPS2553DBVR
U34: TCAN1042HGV; SOIC-8_3.9x4.9mm_P1.27mm

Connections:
+5V: C132.1, C135.1, U32.1 (IN), U32.3 (EN), U34.3 (VCC); also elsewhere on the board
/CAN/CANH: D22.1 (K), FB3.2, J7.2, J8.2, R127.1, R130.2
/CAN/CANL: D22.2 (K), FB3.3, J7.3, J8.3, R131.2, SW1.1
/CAN/CAN_TERM_SW: R128.2, SW1.2
/CAN/CAN_TSPLIT: C134.1, R127.2, R128.1
AUX_5V: C136.1, J7.1, J8.1, U32.6 (OUT); also elsewhere on the board
CAN_RX: U34.4 (RXD); also elsewhere on the board
CAN_TX: U34.1 (TXD); also elsewhere on the board
GND: C132.2, C133.2, C134.2, C135.2, C136.2, D22.3 (A), J7.4, J8.4, R129.2, U32.2 (GND), U34.2 (GND), U34.8 (STB); also elsewhere on the board
unnamed: R129.1, U32.5 (ILIM)
unnamed: FB3.1, R130.1, U34.7 (CANH)
unnamed: FB3.4, R131.1, U34.6 (CANL)
VCC: C133.1, U34.5 (VIO); also elsewhere on the board

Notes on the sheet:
AUX_5V: TPS2553 current-limited ~250mA (R129 sets ILIM). Feeds CAN ports J7/J8 pin 1 and the SPI encoder header (encoders-gpio).
FB3 (CMC DLW32SH101XF2) DNP: shares pads with R130/R131 0R bridges. Default build: 0R populated, straight-through.
Switched split termination: 2x 60R + 4.7nF. SW1 silk: "CAN TERM". Place physically far from BOOT0 jumper.
J7/J8: JST-GH 4-pin, Pixhawk CAN pinout, wired in parallel for daisy chain. D22 TVS at connectors.
5V AUX POWER SWITCH
CAN TRANSCEIVER
SPLIT TERMINATION
CAN CONNECTORS

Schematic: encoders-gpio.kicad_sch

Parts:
C140, C141, C142, C143, C144, C145, C148, C149, C150, C151, C152: 1nF; C_0603_1608Metric
C146, C147: 10uF; C_0805_2012Metric
C153, C154: 1uF; C_0603_1608Metric
C155, C156, C157, C158: 100nF; C_0603_1608Metric
J9: ENC_M0_JST-GH; JST_GH_BM06B-GHS-TBT_1x06-1MP_P1.25mm_Vertical
J10: ENC_M1_JST-GH; JST_GH_BM06B-GHS-TBT_1x06-1MP_P1.25mm_Vertical
J11: ENC_SPI_JST-GH; JST_GH_BM06B-GHS-TBT_1x06-1MP_P1.25mm_Vertical
J12: GPIO_2x4; PinHeader_2x04_P2.54mm_Vertical
R180, R181, R182, R183, R184, R185: 3.3k; R_0603_1608Metric
R186, R187, R188, R189, R190, R191, R197, R198, R199, R200, R201: 100R; R_0603_1608Metric
R192, R193: 56k; R_0603_1608Metric
R194, R195, R196: 470R; R_0603_1608Metric
U30, U31: TPS2553DBV; SOT-23-6; MPN TPS2553DBVR
U35, U36, U37: SN74LVC2G17; SOT-23-6
U38, U39, U41: TPD4E05U06; USON-10_2.5x1.0mm_P0.5mm
U40: SN74LVC1G125; SOT-23-5
U42: TPD1E10B06; D_SOD-523

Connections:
+5V: C153.1, C154.1, U30.1 (IN), U30.3 (EN), U31.1 (IN), U31.3 (EN); also elsewhere on the board
/Encoders & GPIO/ENC_5V_M0: C146.1, J9.1, U30.6 (OUT)
/Encoders & GPIO/ENC_5V_M1: C147.1, J10.1, U31.6 (OUT)
/Encoders & GPIO/ENC_SPI_MISO: J11.4, R195.2
/Encoders & GPIO/ENC_SPI_MOSI: J11.5, R196.2
/Encoders & GPIO/ENC_SPI_NCS: J11.6, U40.4
/Encoders & GPIO/ENC_SPI_SCK: J11.3, R194.2
/Encoders & GPIO/GPIO_1_H: C148.1, J12.3, R197.2, U41.1 (D1+)
/Encoders & GPIO/GPIO_2_H: C149.1, J12.4, R198.2, U41.2 (D1-)
/Encoders & GPIO/GPIO_6_H: C150.1, J12.5, R199.2, U41.4 (D2+)
/Encoders & GPIO/GPIO_7_H: C151.1, J12.6, R200.2, U41.5 (D2-)
/Encoders & GPIO/GPIO_8_H: C152.1, J12.7, R201.2, U42.1 (IO)
/Encoders & GPIO/M0_ENC_A_C: J9.3, R180.2, R186.1, U38.1 (D1+)
/Encoders & GPIO/M0_ENC_A_F: C140.1, R186.2, U35.1
/Encoders & GPIO/M0_ENC_B_C: J9.4, R181.2, R187.1, U38.2 (D1-)
/Encoders & GPIO/M0_ENC_B_F: C141.1, R187.2, U35.3
/Encoders & GPIO/M0_ENC_Z_C: J9.5, R182.2, R188.1, U38.4 (D2+)
/Encoders & GPIO/M0_ENC_Z_F: C142.1, R188.2, U36.1
/Encoders & GPIO/M0_ILIM: R192.1, U30.5 (ILIM)
/Encoders & GPIO/M1_ENC_A_C: J10.3, R183.2, R189.1, U39.1 (D1+)
/Encoders & GPIO/M1_ENC_A_F: C143.1, R189.2, U37.1
/Encoders & GPIO/M1_ENC_B_C: J10.4, R184.2, R190.1, U39.2 (D1-)
/Encoders & GPIO/M1_ENC_B_F: C144.1, R190.2, U37.3
/Encoders & GPIO/M1_ENC_Z_C: J10.5, R185.2, R191.1, U39.4 (D2+)
/Encoders & GPIO/M1_ENC_Z_F: C145.1, R191.2, U36.3
/Encoders & GPIO/M1_ILIM: R193.1, U31.5 (ILIM)
AUX_5V: J11.1; also elsewhere on the board
GND: C140.2, C141.2, C142.2, C143.2, C144.2, C145.2, C146.2, C147.2, C148.2, C149.2, C150.2, C151.2, C152.2, C153.2, C154.2, C155.2, C156.2, C157.2, C158.2, J9.2, J10.2, J11.2, J12.2, J12.8, R192.2, R193.2, U30.2 (GND), U31.2 (GND), U35.2 (GND), U36.2 (GND), U37.2 (GND), U38.3 (GND), U38.8 (GND), U39.3 (GND), U39.8 (GND), U40.1, U40.3 (GND), U41.3 (GND), U41.8 (GND), U42.2 (GND); also elsewhere on the board
GPIO_1: R197.1; also elsewhere on the board
GPIO_2: R198.1; also elsewhere on the board
GPIO_6: R199.1; also elsewhere on the board
GPIO_7: R200.1, U40.2; also elsewhere on the board
GPIO_8: R201.1; also elsewhere on the board
M0_ENC_A: U35.6; also elsewhere on the board
M0_ENC_B: U35.4; also elsewhere on the board
M0_ENC_Z: U36.6; also elsewhere on the board
M0_MOTOR_THERM: J9.6, U38.5 (D2-); also elsewhere on the board
M1_ENC_A: U37.6; also elsewhere on the board
M1_ENC_B: U37.4; also elsewhere on the board
M1_ENC_Z: U36.4; also elsewhere on the board
M1_MOTOR_THERM: J10.6, U39.5 (D2-); also elsewhere on the board
SPI3_MISO: R195.1; also elsewhere on the board
SPI3_MOSI: R196.1; also elsewhere on the board
SPI3_SCK: R194.1; also elsewhere on the board
VCC: C155.1, C156.1, C157.1, C158.1, J12.1, R180.1, R181.1, R182.1, R183.1, R184.1, R185.1, U35.5 (VCC), U36.5 (VCC), U37.5 (VCC), U40.5 (VCC); also elsewhere on the board
